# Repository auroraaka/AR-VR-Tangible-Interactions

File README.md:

# AR-VR-Tangible-Interactions
Created infrared (IR) camera and light attachments for Microsoft Hololens 1 and Oculus Quest 2. SolidWorks and STEP files are provided for CAD models (Hardware>IR_Camera_Apparatus>Microsoft_Hololens_1/Oculus_Quest_2). KiCad files are provided for the PCB and schematic of a compact IR light circuit (Hardware>IR_Camera_Apparatus>IR_Light). 

Programmed computer vision algorithms in Python to detect AruCo codes inside a custom-designed Ping Pong Paddle and Lightsaber. STL files are provided for the empty models and AruCo codes (Hardware>Ping_Pong_Paddle/Lightsaber). 

Mapped object movements to play:
- [Konterball](https://konterball.com/) in a web XR environment using 2D-to-3D conversion system assisted by PyAutoGUI (Software>Konterball).
- [Fruit Ninja](https://github.com/zigurous/unity-fruit-ninja-tutorial) in a wired PC-VR environment using C# scripts in Unity (Sofware>Fruit_Ninja). 

# Quick Links
__**ACM UIST Citation:**__  
Mustafa Doga Dogan, Raul Garcia-Martin, Patrick William Haertel, Jamison John O'Keefe, Ahmad Taka, Akarsh Aurora, Raul Sanchez-Reillo, and Stefanie Mueller. 2023. BrightMarker: 3D Printed Fluorescent Markers for Object Tracking. In Proceedings of the 36th Annual ACM Symposium on User Interface Software and Technology (UIST '23). Association for Computing Machinery, New York, NY, USA, Article 55, 1–13. https://doi.org/10.1145/3586183.3606758

__**Demo Video:**__    
Unlocking the Secret of BrightMarker: 3D Printed Fluorescent Markers for Object Tracking (https://www.youtube.com/watch?v=M5YNR6cVIiM)

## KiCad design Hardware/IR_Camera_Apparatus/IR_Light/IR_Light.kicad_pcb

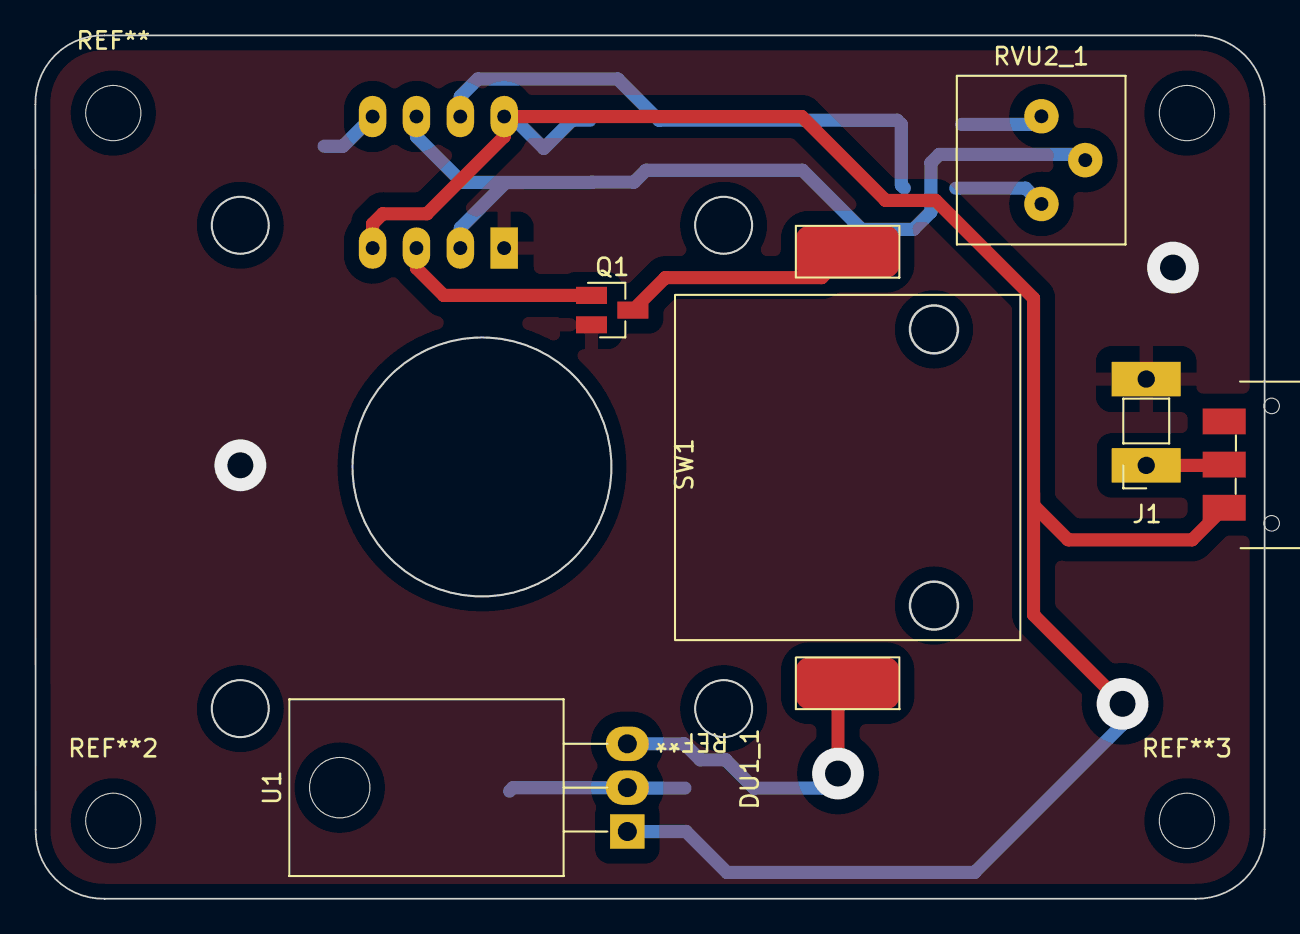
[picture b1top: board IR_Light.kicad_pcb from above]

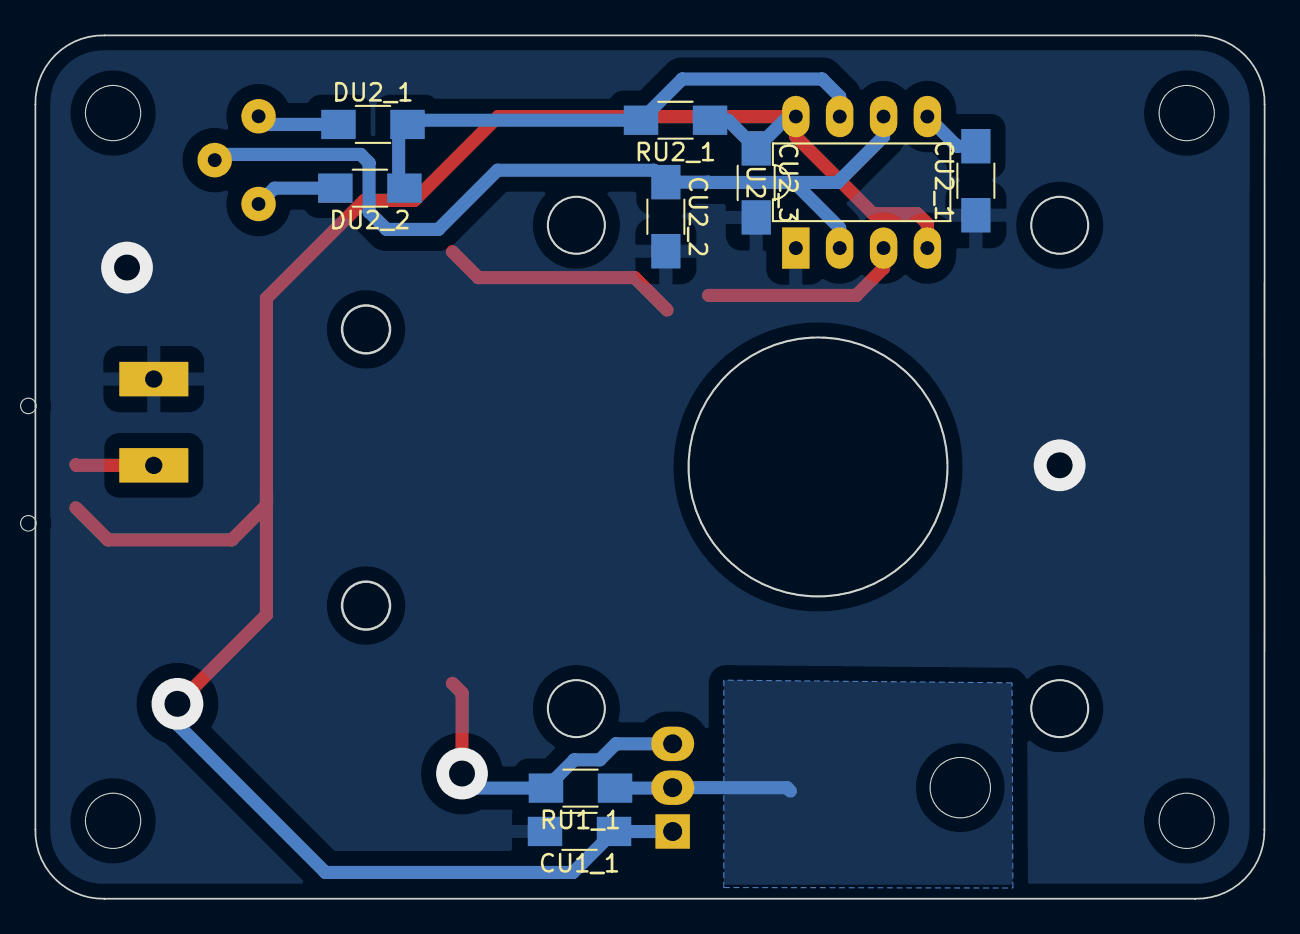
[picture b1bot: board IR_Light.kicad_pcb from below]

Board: 2 copper layers, 71.2 x 50.0 mm, 15 parts (9 on the bottom side), 12 nets.

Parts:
CU1_1, CU2_3: 10uF; C_1206
CU2_1, CU2_2: 10nF; C_1206
DU1_1: LED; IR_LED
DU2_1, DU2_2: 1N4148; R_1206
J1: Power; PinSocket_1x02_P2.54mm_Vertical
Q1: MOSFET_N-CH_30V_1.7A; SOT-23
RU1_1: 12.5; R_1206
RU2_1: 1K; R_1206
RVU2_1: 10K; Potentiometer_Bourns_3386P_Vertical
SW1: Pwr; Switch_SPDT_CnK_JS102011JCQN_9x3.6mm_P2.5mm
U1: LM317L_SO8; TO-220-3_Horizontal_TabDown
U2: LM555xM; DIP-8_W7.62mm_LongPads

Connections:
+9V: CU1_1.1, CU2_3.1, RU2_1.1, SW1.1 (A), U1.1 (VI), U2.4 (R), U2.8 (VCC)
/CTRL: Q1.1 (G), U2.3 (Q)
GND: CU1_1.2, CU2_1.1, CU2_2.2, CU2_3.2, J1.2, Q1.2 (S), U2.1 (GND)
unnamed: CU2_1.2, U2.5 (CV)
unnamed: CU2_2.1, RVU2_1.2, U2.2 (TR), U2.6 (THR)
unnamed: DU1_1.1 (K), Q1.3 (D)
unnamed: DU1_1.2 (A), RU1_1.2, U1.3 (ADJ)
unnamed: DU2_1.1 (K), RVU2_1.3
unnamed: DU2_1.2 (A), DU2_2.1 (K), RU2_1.2, U2.7 (DIS)
unnamed: DU2_2.2 (A), RVU2_1.1
unnamed: J1.1, SW1.2 (B)
unnamed: RU1_1.1, U1.2 (VO)
